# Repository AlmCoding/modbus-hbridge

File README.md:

# MODBUS RTU RS485 40A H-Bridge Module

This H-Bridge module is designed for PWM-controlled DC motor, solenoid, valve, and other DC load applications. It communicates over RS485 using MODBUS RTU, making it easy to integrate into PLC, microcontroller, and PC-based systems without any proprietary protocol.

This 40A H-Bridge is suitable for driving brushed DC motors and other DC loads in industrial, automation, and robotics setups.

## Project folders

- `modbus-hbridge-fw` — Firmware source files for the device, including the embedded software project.  
License: Apache License 2.0.
- `modbus-hbridge-hw` — PCB design files, schematics, and board layout for the H-Bridge hardware.  
License: CERN Open Hardware Licence Version 2.
- `modbus-hbridge-3d` — 3D printable enclosure files and case models for the module.  
License: CERN Open Hardware Licence Version 2.

## Python library

Control the device using the Python library repository:
https://github.com/AlmCoding/modbus-py

## Purchase options

The device is available for purchase on Tindie:
https://www.tindie.com/products/almcoding/modbus-rtu-rs485-40a-h-bridge-module/

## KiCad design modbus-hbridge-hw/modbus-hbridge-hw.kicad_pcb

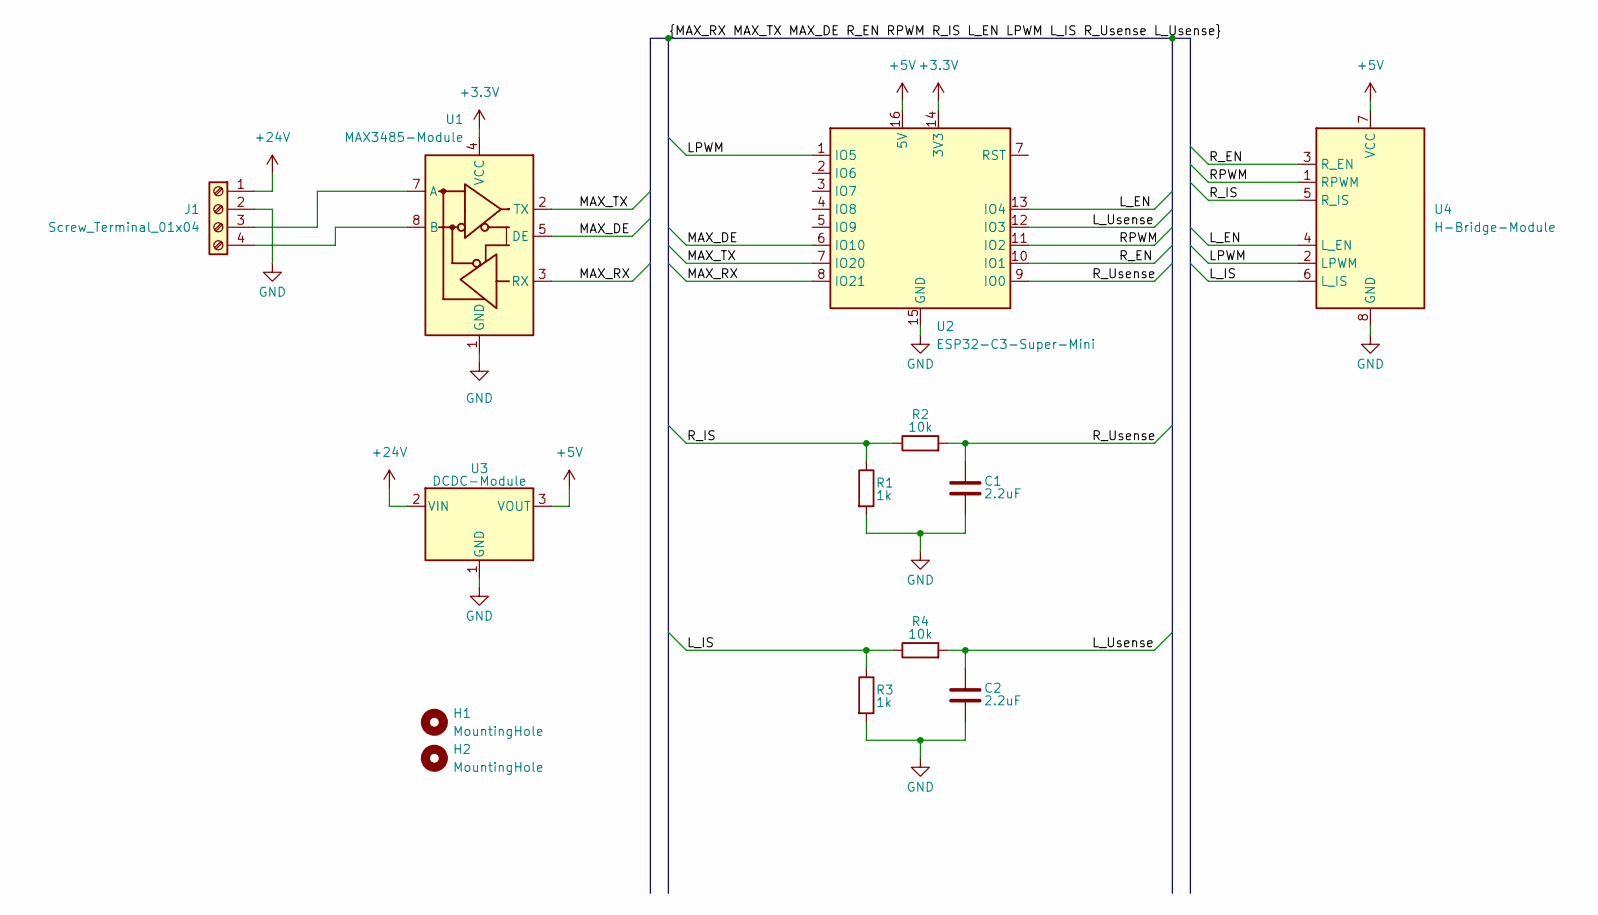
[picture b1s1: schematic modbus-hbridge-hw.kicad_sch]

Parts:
C1, C2: 2.2uF; C_0603_1608Metric_Pad1.08x0.95mm_HandSolder
H1, H2: MountingHole; MountingHole_3.2mm_M3
J1: Screw_Terminal_01x04; TerminalBlock_CUI_TB007-508-04_1x04_P5.08mm_Horizontal
R1, R3: 1k; R_0603_1608Metric_Pad0.98x0.95mm_HandSolder
R2, R4: 10k; R_0603_1608Metric_Pad0.98x0.95mm_HandSolder
U1: MAX3485-Module
U2: ESP32-C3-Super-Mini; ESP32-C3-SuperMini
U3: DCDC-Module; DCDC-Module-S
U4: H-Bridge-Module

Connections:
+3.3V: U1.4 (VCC), U2.14 (3V3)
+5V: U2.16 (5V), U3.3 (VOUT), U4.7 (VCC)
+24V: J1.1, U3.2 (VIN)
/LPWM: U2.1 (IO5), U4.2 (LPWM)
/L_EN: U2.13 (IO4), U4.4 (L_EN)
/L_IS: R3.1, R4.1, U4.6 (L_IS)
/L_Usense: C2.1, R4.2, U2.12 (IO3)
/MAX_DE: U1.5 (DE), U2.6 (IO10)
/MAX_RX: U1.3 (RX), U2.8 (IO21)
/MAX_TX: U1.2 (TX), U2.7 (IO20)
/RPWM: U2.11 (IO2), U4.1 (RPWM)
/R_EN: U2.10 (IO1), U4.3 (R_EN)
/R_IS: R1.1, R2.1, U4.5 (R_IS)
/R_Usense: C1.1, R2.2, U2.9 (IO0)
GND: C1.2, C2.2, J1.2, R1.2, R3.2, U1.1 (GND), U1.6 (GND), U2.15 (GND), U3.1 (GND), U3.4 (GND), U4.8 (GND)
unnamed: J1.3, U1.7 (A)
unnamed: J1.4, U1.8 (B)

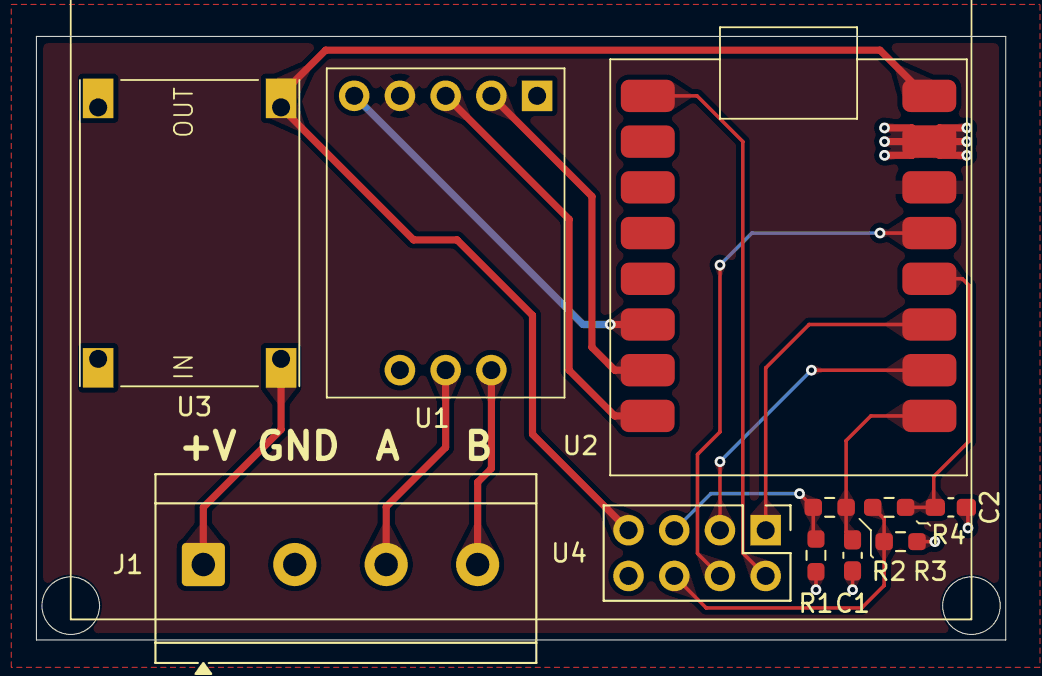
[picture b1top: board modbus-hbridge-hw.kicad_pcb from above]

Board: 2 copper layers, 53.8 x 33.5 mm, 13 parts (0 on the bottom side), 17 nets.

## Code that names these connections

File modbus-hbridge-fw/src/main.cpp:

#include "common.h"
#include <Arduino.h>
#include <HBridge.h>
#include <Modbus.h>

#define DEBUG_ENABLE_MAIN 1
#if ((DEBUG_ENABLE_MAIN == 1) && (ENABLE_DEBUG_OUTPUT == 1))
#define DEBUG_INFO(f, ...) debugPrint("[INF][Main]", f, ##__VA_ARGS__)
#define DEBUG_ERROR(f, ...) debugPrint("[ERR][Main]", f, ##__VA_ARGS__)
#else
#define DEBUG_INFO(...)
#define DEBUG_ERROR(...)
#endif

// ESP32-C3 Pin Configuration
// H-Bridge Pins
const uint8_t L_IS_PIN = 3;  // Left Current Sense
const uint8_t L_EN_PIN = 4;  // Left Enable
const uint8_t L_PWM_PIN = 5; // Left PWM
const uint8_t R_IS_PIN = 0;  // Right Current Sense
const uint8_t R_EN_PIN = 1;  // Right Enable
const uint8_t R_PWM_PIN = 2; // Right PWM

// RS485 Modbus Pins
const uint8_t MODBUS_RX_PIN = 20; // UART1 RX
const uint8_t MODBUS_TX_PIN = 21; // UART1 TX
const uint8_t MODBUS_RE_PIN = 10; // RS485 driver enable

const uint8_t LED_PIN = 8; // On-board LED pin
const uint32_t LED_TOGGLE_INTERVAL_MS = 250;

// Create H-Bridge and Modbus instances
HBridge hbridge(L_IS_PIN, L_EN_PIN, L_PWM_PIN, R_IS_PIN, R_EN_PIN, R_PWM_PIN);
Modbus modbus(MODBUS_RX_PIN, MODBUS_TX_PIN, MODBUS_RE_PIN, hbridge);

void setup() {
  setCpuFrequencyMhz(160);

  pinMode(LED_PIN, OUTPUT);
  digitalWrite(LED_PIN, HIGH);

#if (ENABLE_DEBUG_OUTPUT == 1)
  delay(3000);
  Serial.begin(921600);
  while (!Serial) {
    delay(100);
  }
#endif

  DEBUG_INFO(DIVIDER);
  DEBUG_INFO("Setup Modbus H-Bridge [...]");
  DEBUG_INFO("Firmware version: %s", FIRMWARE_VERSION);
  DEBUG_INFO("Free heap: %u bytes", ESP.getFreeHeap());
  DEBUG_INFO("CPU frequency: %d MHz", getCpuFrequencyMhz());

  // Initialize H-Bridge
  hbridge.begin();
  hbridge.enableLeft(true);
  hbridge.enableRight(true);
  hbridge.setRightPwm(0); // Start with 0 PWM
  hbridge.setLeftPwm(0);  // Start with 0 PWM

  // Initialize Modbus RTU
  modbus.begin();

  DEBUG_INFO("Setup Modbus H-Bridge [OK]");
  DEBUG_INFO(DIVIDER);
}

void loop() {
  // Process Modbus commands
  modbus.update();

  hbridge.poll();

  // Toggle LED for heartbeat
  static uint32_t lastToggleTime = 0;
  uint32_t currentTime = millis();
  if (currentTime - lastToggleTime >= LED_TOGGLE_INTERVAL_MS) {
    lastToggleTime = currentTime;
    digitalWrite(LED_PIN, !digitalRead(LED_PIN));
  }
}

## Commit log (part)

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2026-04-03 Add codebase
2026-04-04 Add debugging output
2026-04-10 Fix PWM resolution
2026-06-16 Prepare current sensing
